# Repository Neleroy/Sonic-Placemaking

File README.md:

# Sonic-Placemaking
A repository for DIY experimental instruments, created for the [Centre for Art Tapes' 2025-26 Media Art Scholarship](https://www.cfat.ca/mas-2026).

The 38th Annual Media Arts Scholarship Exhibition, entitled Here and Now, was held at the Centre for Art Tapes in Halifax, Nova Scotia from March 20th to April 3rd, 2026. My contribution was a series of six experimental electronic instruments (with all but one having an additional companion module), hung from the ceiling by their audio cables. All electronics, save for the Digi-Quack, are hand-assembled and analogue. All enclosures were converted into STLs with the aid of Hunyuan3D (https://huggingface.co/spaces/tencent/Hunyuan3D-2.1), and were printed by Mable Monroe (https://github.com/cypaloma).

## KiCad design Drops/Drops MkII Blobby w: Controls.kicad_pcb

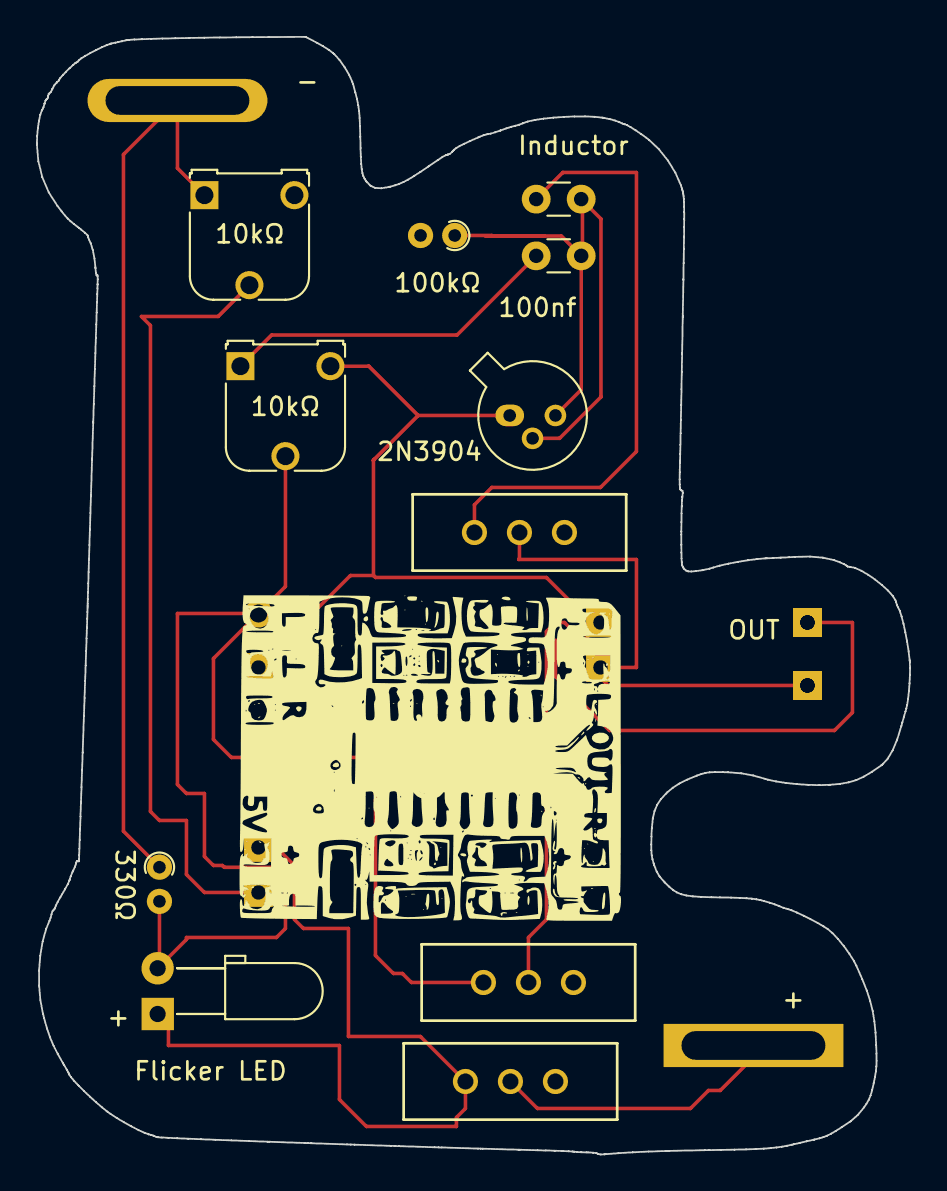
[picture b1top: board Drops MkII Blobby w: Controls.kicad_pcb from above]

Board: 2 copper layers, 48.5 x 62.1 mm, 5 parts (0 on the bottom side), 4 nets.

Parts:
C2: 100nf; C_Disc_D3.0mm_W1.6mm_P2.50mm
Inductor: 1uf; C_Disc_D3.0mm_W1.6mm_P2.50mm
Q1: 2N3904; TO-18-3
R1: 100kΩ; R_Axial_DIN0204_L3.6mm_D1.6mm_P1.90mm_Vertical
RV1: 10kΩ; Potentiometer_Runtron_RM-065_Vertical

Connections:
GND: Q1.1 (E), RV1.3
unnamed: C2.1, RV1.1
unnamed: C2.2, Q1.3 (C), R1.1
unnamed: Inductor.2, Q1.2 (B)

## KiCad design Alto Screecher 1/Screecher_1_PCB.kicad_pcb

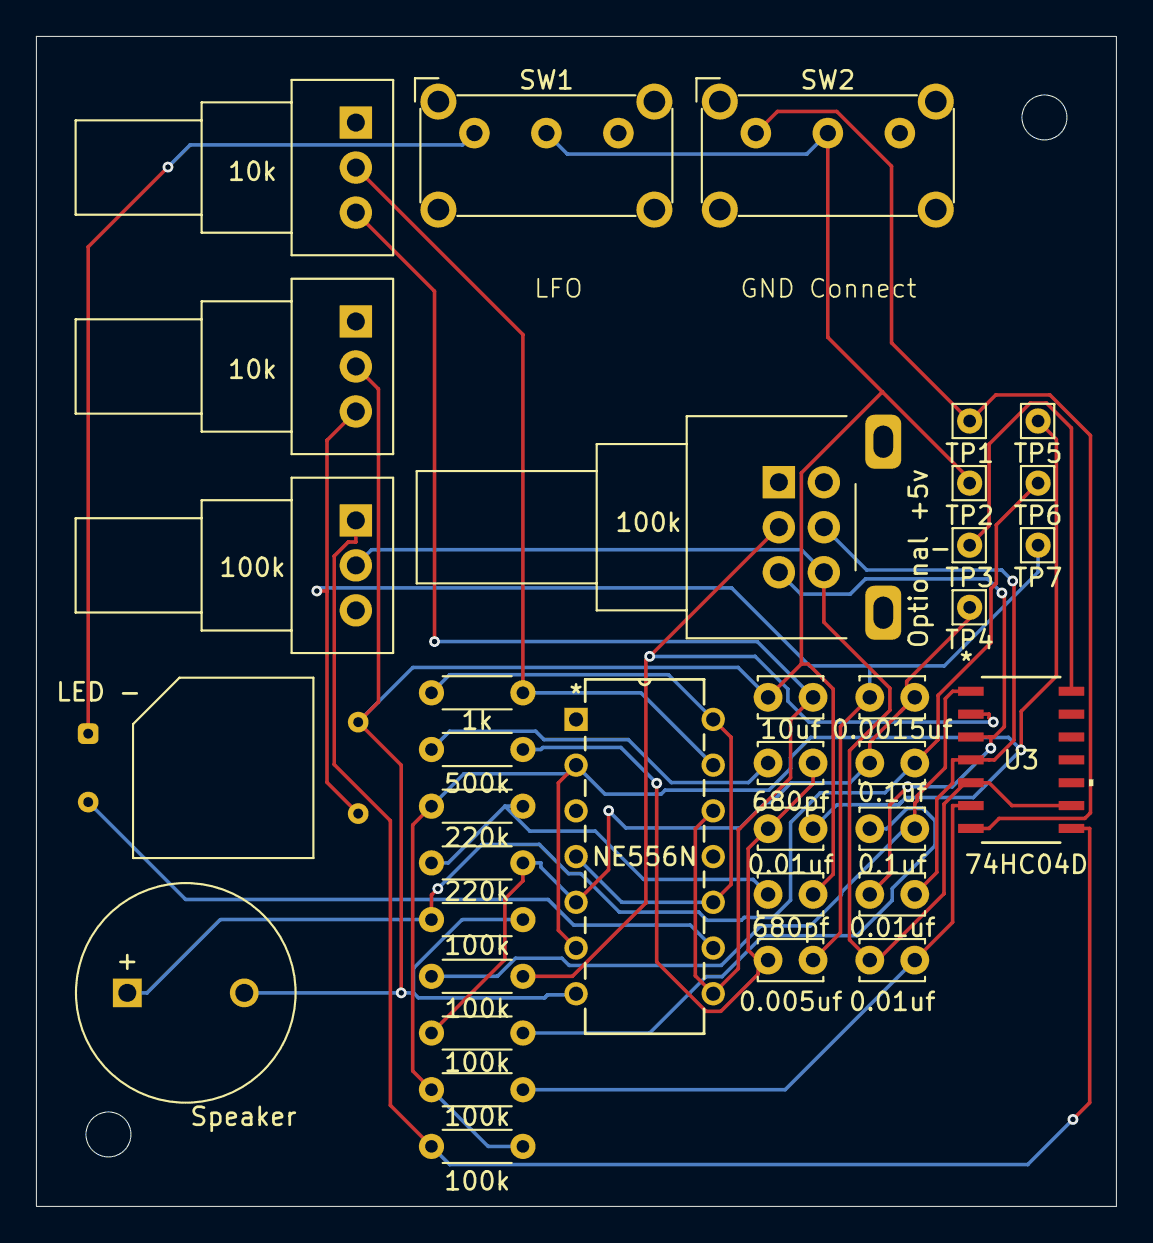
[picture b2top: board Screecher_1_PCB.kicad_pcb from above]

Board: 2 copper layers, 60.0 x 65.0 mm, 36 parts (0 on the bottom side), 23 nets.

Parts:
C1: 10uf; C_Disc_D3.4mm_W2.1mm_P2.50mm
C2, C4: 680pf; C_Disc_D3.4mm_W2.1mm_P2.50mm
C3, C9, C10: 0.01uf; C_Disc_D3.4mm_W2.1mm_P2.50mm
C5: 0.005uf; C_Disc_D3.4mm_W2.1mm_P2.50mm
C6: 0.0015uf; C_Disc_D3.4mm_W2.1mm_P2.50mm
C7, C8: 0.1uf; C_Disc_D3.4mm_W2.1mm_P2.50mm
LS1: Speaker; MagneticBuzzer_ProSignal_ABT-410-RC
R1: 1k; R_Axial_DIN0204_L3.6mm_D1.6mm_P5.08mm_Horizontal
R2: 500k; R_Axial_DIN0204_L3.6mm_D1.6mm_P5.08mm_Horizontal
R3, R4: 220k; R_Axial_DIN0204_L3.6mm_D1.6mm_P5.08mm_Horizontal
R5, R6, R7, R8, R9: 100k; R_Axial_DIN0204_L3.6mm_D1.6mm_P5.08mm_Horizontal
RV1, RV2: 10k; Potentiometer_Alps_RK09Y11_Single_Horizontal
RV3: 100k; Potentiometer_Alps_RK09L_Double_Horizontal
RV4: 100k; Potentiometer_Alps_RK09Y11_Single_Horizontal
SW1, SW2: SW_SPDT; SW_E-Switch_EG1224_SPDT_Angled
TP1: TOUCH1; Pin_D0.7mm_L6.5mm_W1.8mm_FlatFork
TP2: TOUCH2; Pin_D0.7mm_L6.5mm_W1.8mm_FlatFork
TP3: Optional +5v; Pin_D0.7mm_L6.5mm_W1.8mm_FlatFork
TP4: TOUCH 3; Pin_D0.7mm_L6.5mm_W1.8mm_FlatFork
TP5: TOUCH 4; Pin_D0.7mm_L6.5mm_W1.8mm_FlatFork
TP6: TOUCH 5; Pin_D0.7mm_L6.5mm_W1.8mm_FlatFork
TP7: TOUCH 6; Pin_D0.7mm_L6.5mm_W1.8mm_FlatFork
U1: NE556N; N14
U2: VTL5C; PerkinElmer_VTL5C
U3: 74HC04D; SOIC14_TOS

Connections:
+5V: R1.1, U1.4 (1RESET), U1.10 (2RESET), U1.14 (VCC)
GNDREF: C1.1, C4.2, LS1.2, R5.2, RV2.2, SW1.2 (B), SW2.2 (B), TP2.1, U1.7 (GND), U2.3
unnamed: C2.1, R2.1
unnamed: C2.2, C3.1, C5.1, R2.2
unnamed: C4.1, R3.2, R4.1
unnamed: C5.2, C6.1, RV2.3, TP7.1, U2.4
unnamed: C7.2, LS1.1, R5.1, TP6.1
unnamed: C8.1, R7.2
unnamed: C8.2, R6.1, U3.1
unnamed: C9.1, RV3.3, U3.3
unnamed: C9.2, RV3.5, U3.4
unnamed: C10.1, RV3.6, RV4.2, U3.5, U3.9
unnamed: C10.2, R8.2, U3.6
unnamed: R6.2, RV3.2, U3.2
unnamed: R9.1, RV4.1, U3.8
unnamed: SW1.1 (A), U2.1 (-)
unnamed: SW2.1 (A), TP1.1, U3.7
unnamed: TP3.1, U3.14
unnamed: C6.2, C7.1, R4.2, R7.1, TP4.1, U1.5 (1OUT)
unnamed: C3.2, R3.1, R8.1, R9.2, TP5.1, U1.2 (1THRES), U1.6 (1TRIG)
unnamed: R1.2, RV1.2, U1.13 (2DISCH)
unnamed: U1.9 (2OUT), U2.2 (+)
unnamed: C1.2, RV1.3, U1.8 (2TRIG), U1.12 (2THRES)

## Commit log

2026-03-11 Create Soprano Screech Manual
2026-03-11 Update Soprano Screech Manual
2026-03-30 Create Digi-Quack Manual
2026-03-30 Create Alto Screecher 1 Manual
2026-03-30 Create Alto Screecher 2 Manual
2026-03-30 Create Quackembouche Manual
2026-03-30 Create Pesudo Seq Manual
2026-03-30 Update Pesudo Seq Manual
2026-03-30 Create Drops Manual
2026-03-30 Update Drops Manual
2026-03-30 Create Qollision Quack Manual
2026-04-04 Updated folder name
